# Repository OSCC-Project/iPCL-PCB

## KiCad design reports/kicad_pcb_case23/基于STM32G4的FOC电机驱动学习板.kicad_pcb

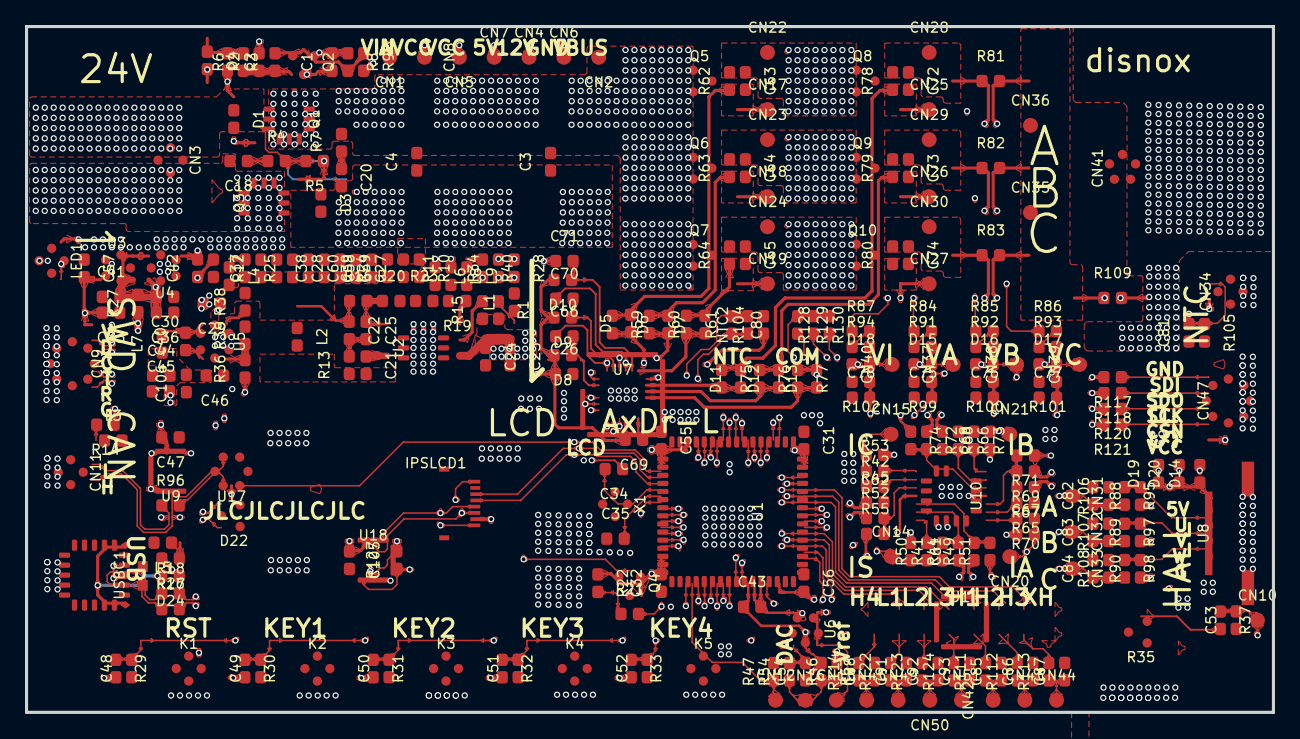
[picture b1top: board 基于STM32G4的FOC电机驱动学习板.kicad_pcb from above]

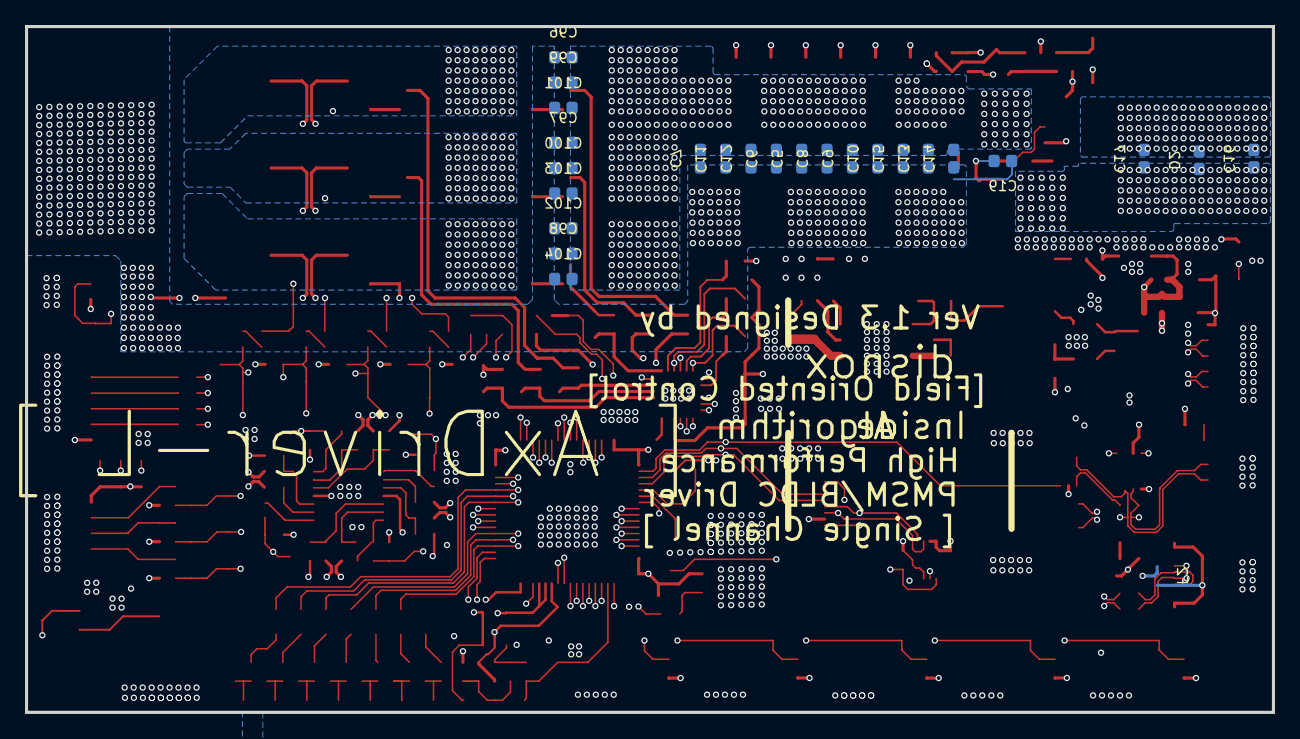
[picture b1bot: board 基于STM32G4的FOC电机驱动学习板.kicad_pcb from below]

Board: 4 copper layers, 100.0 x 55.0 mm, 334 parts (25 on the bottom side), 160 nets.

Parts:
C1, C2, C18, C19, C20, C26, C27, C28, C30, C31, C32, C33, C36, C37, C38, C39, C41, C42, C43, C44, C45, C46, C47, C48, C49, C50, C51, C52, C54, C55, C56, C57, C58, C59, C60, C61, C62, C63, C64, C65, C66, C67, C68, C69, C70, C71, C72, C73, C74, C75, C76, C77, C78, C80, C81, C82, C83, C84, C85, C86, C87, C88, C91, C92, C93, C105, C106: ef8bc71f18f14a2b8407a1c75c1857de
C3, C4: c59c3b7d6ca345ddb948f05971adbf39
C5, C6, C7, C8, C9, C10, C11, C12, C13, C14, C15, C16, C17, C29, C96, C97, C98, C99, C100, C101, C102, C103, C104: 562d9c395cfd4d56965eed8567f4960b
C21, C22, C25, C34, C35, C53: 7e8c87f61e8d48fe9289105f4e4eab7a
C23, C24: ac686b6caae446ffbbcca766a5ee3a01
C40: 47206a73ba6b4fccaee19337958ce421
CN1, CN2, CN4, CN5, CN6, CN7, CN8, CN10, CN12, CN13, CN14, CN15, CN16, CN17, CN18, CN19, CN20, CN21, CN22, CN23, CN24, CN25, CN26, CN27, CN28, CN29, CN30, CN31, CN32, CN33, CN35, CN36, CN37, CN38, CN39, CN40, CN42, CN43, CN44, CN45, CN49, CN50, CN51: fd3b323368aa491987dd5c73ade3f9d4
CN3: f1c4b56d3fa5492a905759f758d03d4e
CN9: e7604
CN11: e551
CN34: 72928b0395164ccbb3ac6d1df7a36019
CN41: 238db645694445ce824d8680ce8e221c
CN47: e0abee4a9a5b4604a238f3efeac42c31
D1, D3: 59eef894ab204f08bb19d40773817b76
D2: c2d7f1bae8b545698492e2dec6af670e
D4: 4f0528e9bede4f3ebeeda6dc7a85a460
D5, D6, D7, D11, D12, D13, D14, D15, D16, D17, D18, D19, D20, D24: f5361794368045b4a1b76496df9a3818
D8, D9, D10: 63cfcbcd9a284726b99ba225908b0e3a
D22: e166
F2: F0603
IPSLCD1: 焊接式_TFT_1.14_135X240_13PIN
J1: 507fd03bec4d44e5ae0a3a3c9a755e1a
K1, K2, K3, K4, K5: 38b16b919dc84e3a93c34e285811859a
L1, L3, L4, L5, L6, L8, L9: 15744c9fbac84e36ba33635dcccc2dd5
L2: 5eb3ba56938d4ba998db27fa04a57f61
L7: dccf333eac264c8c867efbfa5430a8ec
LED1: 92a6220bcf694ea1b484849a5b704caf
NTC2: 3ca690dd11e941f3ae1f3810a823019c
Q1, Q3: c54244fc48a749cda057cc0810780ba0
Q2: e50
Q4: e54
Q5, Q6, Q7, Q8, Q9, Q10: 5eed3b8ce67d409d8b6777258f1d9ffc
R1, R2, R3, R4, R5, R6, R7, R8, R9, R10, R11, R12, R14, R17, R18, R21, R22, R23, R24, R25, R26, R28, R29, R30, R31, R32, R33, R34, R37, R38, R40, R41, R42, R44, R45, R46, R47, R49, R50, R51, R52, R53, R54, R55, R57, R59, R60, R61, R62, R63, R64, R65, R66, R67, R68, R69, R70, R71, R72, R73, R74, R75, R76, R77, R78, R79, R80, R84, R85, R86, R87, R88, R89, R90, R91, R92, R93, R94, R95, R96, R97, R98, R99, R100, R101, R102, R104, R105, R106, R107, R108, R111, R112, R113, R114, R117, R118, R120, R121, R122, R123, R124, R127, R128, R129, R130: 3ca690dd11e941f3ae1f3810a823019c
R13, R15, R16, R19, R20: 7ca7a77a3c9a400a97f53773ae813252
R27, R36, R39: 7367616b648e4f089aa157a019dffa0b
R35: 079bee4ddd7a4396947f4deb10ada5d4
R81, R82, R83, R109: 9ad5a23cb50249ce82f923a95eb729c2
U1: e516
U2: 4fce1811ce044460a077a6a809735f86
U3: 2a1686e7c31848c09f9be7f9abc50536
U4: d97cf38101c64b749d9a7557fd111860
U5: 01fc61f14587464abc2342bbf474e4db
U6: d283220f0d3f47a3be0904fa3adf1f94
U7: 71895e02d11d4488b91a4eac142d4aa9
U8: conn-smd_5p-p1.25_xunpu_wafer-gh1.25-5pwb
U9: e3
U10: cc8f16f358a44a98967478fccaae8a8c
U17: 8034ca89fcaa42d08be80f2405998dfa
U18: 629a12d09f554d80887da3093acdb491
USBC1: e188
X1: 3fcb4c6e8928476cb18f6d5142511c4e

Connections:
5V: C30.2, C36.2, C41.2, C47.2, CN7.1, D14.1, D19.1, D20.1, D24.1, J1.15, LED1.3, R26.2, R27.2, U3.1, U3.3, U4.1, U4.3, U8.5, U9.3
12V: C22.1, C26.1, C27.2, C28.2, C29.2, C37.1, C38.2, C39.1, C58.2, C59.2, C60.2, C69.2, CN4.1, D8.2, D9.2, D10.2, L2.2, R16.1, R25.2, R38.2, U5.5, U7.4
$1N7256: C18.1, R4.1
$1N10553: C2.1, Q2.1, R2.1, R6.1
$1N11589: C19.1, D3.1, Q3.1, R5.1
$1N11866: D4.1, R3.1, R6.2
$1N12961: C20.1, R7.1
$1N15998: C2.2, Q2.3, R8.2, R9.1
$1N55849: C63.2, CN17.1, D5.2, Q5.1, R59.1, R62.1
$1N56388: C72.2, CN25.1, D11.2, Q8.1, R75.1, R78.1
$1N57486: C64.2, CN18.1, D6.2, Q6.1, R60.1, R63.1
$1N57488: C73.2, CN26.1, D12.2, Q9.1, R76.1, R79.1
$1N58344: C65.2, CN19.1, D7.2, Q7.1, R61.1, R64.1
$1N58346: C74.2, CN27.1, D13.2, Q10.1, R77.1, R80.1
$1N74659: R52.2, R55.2, U10.3
$1N75153: R42.2, R45.2, U10.2
$1N75339: R42.1, R53.2, U10.1
$1N78360: R41.1, R50.2, U10.7
$1N78363: R49.2, R51.2, U10.5
$1N78364: R41.2, R44.2, U10.6
$1N79721: R66.1, R73.2, U10.14
$1N79723: R72.2, R74.2, U10.12
$1N79724: R66.2, R68.2, U10.13
$1N80505: R65.1, R70.2, U10.8
$1N80507: R69.2, R71.2, U10.10
$1N80508: R65.2, R67.2, U10.9
$1N96819: R84.2, R91.1
$1N96824: R85.2, R92.1
$1N96829: R87.2, R94.1
$1N96834: R86.2, R93.1
$1N107842: R88.2, R95.1, U8.4
$1N108105: R89.2, R97.1, U8.3
$1N108370: R90.2, R98.1, U8.2
$1N130103: L9.1, R40.1
$1N130414: L8.1, R34.2
$1N134680: L5.1, R26.1
$1N145652: CN47.5, R117.1
$1N145656: CN47.4, R118.1
$1N145660: CN47.3, R120.1
$1N145664: CN47.2, R121.1
$1N245778: R36.2, R39.1, U5.3
$1N245779: C40.2, L7.1, U5.6
$1N245780: C40.1, U5.1
$1N268846: L3.1, R14.2
$1N269486: L1.1, R1.1
$1N270139: C85.1, CN42.1, R111.1
$1N270143: J1.9, R111.2
$1N270253: C91.1, CN49.1, R122.1
$1N270255: J1.3, R122.2
$1N270473: C86.1, CN43.1, R112.1
$1N270475: J1.11, R112.2
$1N270480: C92.1, CN50.1, R123.1
$1N270482: J1.5, R123.2
$1N270701: C87.1, CN44.1, R113.1
$1N270703: J1.13, R113.2
$1N270708: C93.1, CN51.1, R124.1
$1N270710: J1.7, R124.2
$1N398404: C1.2, D1.2, Q1.1, R8.1
$1N441583: C88.1, CN45.1, R114.1
$1N441584: J1.1, R114.2
$1N704042: L6.1, R28.1
$1N752227: CN16.1, R46.1, R54.1, R57.2
$1N807322: R35.2, R37.2
$1N846235: R38.1, U5.4
$1N858763: C54.2, R47.2, R54.2, U6.1
$1N920711: Q4.1, R21.1, R22.2
$1N958663: C44.2, C45.2, C46.2, C106.2, L7.2, R27.1, R36.1
$1N1062496: L4.1, R25.1
$1N1062500: R19.1, U2.4
$1N1062505: C22.2, C25.2, R13.2
$1N1062506: C21.2, L2.1, R13.1, U2.8
$1N1062507: R15.2, U2.3
$1N1062508: C21.1, U2.7
$1N1322078: R96.2, U17.4
$1N1473399: J1.16, R88.1, R89.1, R90.1
$1N1599202: D24.2, F2.2
ADSPE: C53.2, CN10.1, R37.1, U1.22
AGND: C42.1, C43.1, C54.1, C61.1, C62.1, C67.1, C68.1, R12.1, R57.1, U1.27, U6.2, U10.11
APH4: J1.2, U1.11
AVCC: C42.2, C43.2, CN8.1, R46.2, U1.28, U1.29, U4.5, U6.5, U10.4
BDM: R17.2, U1.45
BDP: R18.2, U1.46
CAN_H: CN11.2, D22.1, U9.7, U17.3
CAN_L: CN11.1, D22.2, R96.1, U9.6
CAN_RX: U1.61, U9.4
CAN_TX: U1.62, U9.1
CLK: CN9.3, U1.50
COM: R128.2, R129.1, R130.1, U1.26
DAC: CN12.1, R47.1, U1.18
DCBUS: C3.1, C4.1, C5.2, C6.2, C7.2, C8.2, C9.2, C10.2, C11.2, C12.2, C13.2, C14.2, C15.2, C23.2, C24.2, C96.2, C97.2, C98.2, C99.2, C100.2, C101.2, C102.2, C103.2, C104.2, CN2.1, Q1.2, Q5.2, Q6.2, Q7.2, R1.2, R2.2, R7.2, R15.1, R87.1, U2.2
DCBUS_IN: C1.1, C16.2, C17.2, CN1.1, CN3.1, D1.1, D2.2, Q1.3, Q2.2, R3.2, R4.2, R5.2
DIO: CN9.2, U1.49
FB: C25.1, R16.2, R20.1, U2.5
GND: C23.1, C24.1, C26.2, C27.1, C28.1, C29.1, C30.1, C31.1, C32.1, C33.1, C34.1, C35.1, C36.1, C37.2, C38.1, C39.2, C41.1, C44.1, C45.1, C46.1, C47.1, C48.1, C49.1, C50.1, C51.1, C52.1, C53.1, C55.1, C56.1, C57.1, C58.1, C59.1, C60.1, C69.1, C75.1, C76.1, C77.1, C78.1, C80.1, C81.1, C82.2, C83.2, C84.2, C85.2, C86.2, C87.2, C88.2, C91.2, C92.2, C93.2, C105.2, C106.1, CN6.1, CN9.6, CN9.7, CN9.8, CN11.3, CN11.4, CN34.3, CN34.4, CN47.6, CN47.7, CN47.8, D22.3, IPSLCD1.2, IPSLCD1.9, IPSLCD1.10, K1.1, K2.1, K3.1, K4.1, K5.1, L1.2, L3.2, L4.2, L5.2, L6.2, L8.2, L9.2, LED1.1, NTC2.2, R10.2, R11.2, R12.2, R19.2, R20.2, R23.1, R23.2, R24.1, R24.2, R35.3, R39.2, R99.2, R100.2, R101.2, R102.2, R105.2, R106.2, R107.2, R108.2, U1.15, U1.31, U1.47, U1.63, U2.1, U2.9, U3.2, U4.2, U5.2, U7.6, U7.25, U8.1, U8.6, U8.7, U9.2, U9.8, U9.9, U17.2, U18.4, U18.9, USBC1.0, USBC1.A1, USBC1.A12, USBC1.B1, USBC1.B12, X1.2, X1.4
HALL_A: C82.1, CN31.1, D19.2, R95.2, R106.1, U1.20
HALL_B: C83.1, CN32.1, D20.2, R97.2, R107.1, U1.21
HALL_C: C84.1, CN33.1, D14.2, R98.2, R108.1, U1.24
HIN1: J1.10, U1.42, U7.22
HIN2: J1.12, U1.43, U7.23
HIN3: J1.14, U1.44, U7.24
HO1: D5.1, R59.2, U7.19
HO2: D6.1, R60.2, U7.16
HO3: D7.1, R61.2, U7.13
IA: C67.2, CN20.1, R70.1, U1.14
IA+: C72.1, CN28.1, Q8.3, R69.1, R78.2, R81.1
IA-: CN35.1, CN36.1, R45.1, R49.1, R67.1, R68.1, R81.2, R82.2, R83.2, R109.1
IB: C68.2, CN21.1, R73.1, U1.13
IB+: C73.1, CN29.1, Q9.3, R72.1, R79.2, R82.1
IBUS: C61.2, CN14.1, R50.1, U1.17
IC: C62.2, CN15.1, R53.1, U1.12
IC+: C74.1, CN30.1, Q10.3, R52.1, R80.2, R83.1
KEY1: C49.2, K2.2, R30.1, U1.41
KEY2: C50.2, K3.2, R31.1, U1.40
KEY3: C51.2, K4.2, R32.1, U1.39
KEY4: C52.2, K5.2, R33.1, U1.38
LCD_BLK: R21.2, U1.60
LCD_CS: IPSLCD1.8, U1.59
LCD_DC: IPSLCD1.4, R40.2, U1.4
LCD_RES: IPSLCD1.3, R34.1, U1.3
LEDK: IPSLCD1.1, Q4.3
LIN1: J1.4, U1.35, U7.1
LIN2: J1.6, U1.36, U7.2
LIN3: J1.8, U1.37, U7.3
LO1: D11.1, R75.2, U7.11
LO2: D12.1, R76.2, U7.10
LO3: D13.1, R77.2, U7.9
MA: C63.1, C66.1, CN22.1, CN41.3, Q5.3, Q8.2, R62.2, R84.1, U7.18
MB: C64.1, C70.1, CN23.1, CN41.2, Q6.3, Q9.2, R63.2, R85.1, U7.15
MC: C65.1, C71.1, CN24.1, CN41.1, Q7.3, Q10.2, R64.2, R86.1, U7.12
NRST: C48.2, K1.2, R29.1, U1.7
NTC1: C80.2, NTC2.1, R104.2, U1.25
NTC3: C81.2, CN34.2, R105.1, U1.34
O_IN: C34.2, U1.5, X1.1
O_OUT: C35.2, U1.6, X1.3
PGND: C3.2, C4.2, C5.1, C6.1, C7.1, C8.1, C9.1, C10.1, C11.1, C12.1, C13.1, C14.1, C15.1, C19.2, C20.2, C96.1, C97.1, C98.1, C99.1, C100.1, C101.1, C102.1, C103.1, C104.1, CN41.4, CN41.5, D3.2, Q3.3, R9.2, R10.1, R11.1, R44.1, R109.2
PGND_IN: C16.1, C17.1, C18.2, CN3.2, D2.1, D4.2, Q3.2
RGB: LED1.2, U1.19
RX_TX: CN9.5, U1.33
R_EN: R28.2, U1.2, U17.6
SPI1_CSN: R121.2, U1.55
SPI1_MISO: R118.2, U1.57
SPI1_MOSI: R117.2, U1.58
SPI1_SCK: R120.2, U1.56
SPI3_CSN: R127.1, U1.51, U18.1
SPI3_MISO: U1.53, U18.2
SPI3_MOSI: IPSLCD1.5, U1.54, U18.5
SPI3_SCK: IPSLCD1.6, U1.52, U18.6
TX_RX: CN9.4, U1.30
USB_5V: F2.1, USBC1.A4, USBC1.A9, USBC1.B4, USBC1.B9
USB_DM: R17.1, USBC1.A7, USBC1.B7
USB_DP: R18.1, USBC1.A6, USBC1.B6
VA: C75.2, CN37.1, D15.2, R91.2, R99.1, R128.1, U1.8
VB: C76.2, CN38.1, D16.2, R92.2, R100.1, R130.2, U1.9
VB1: C66.2, D8.1, U7.20
VB2: C70.2, D9.1, U7.17
VB3: C71.2, D10.1, U7.14
VBUS: C78.2, CN40.1, D18.2, R94.2, R102.1, U1.23
VC: C77.2, CN39.1, D17.2, R93.2, R101.1, R129.2, U1.10
VCC: C31.2, C32.2, C33.2, C55.2, C56.2, C57.2, C105.1, CN5.1, CN9.1, CN34.1, CN47.1, D15.1, D16.1, D17.1, D18.1, IPSLCD1.7, Q4.2, R14.1, R22.1, R29.2, R30.2, R31.2, R32.2, R33.2, R35.1, R104.1, R127.2, U1.1, U1.16, U1.32, U1.48, U1.64, U3.5, U9.5, U17.5, U18.3, U18.7, U18.8
VREF: CN13.1, R51.1, R55.1, R71.1, R74.1, U6.3, U6.4

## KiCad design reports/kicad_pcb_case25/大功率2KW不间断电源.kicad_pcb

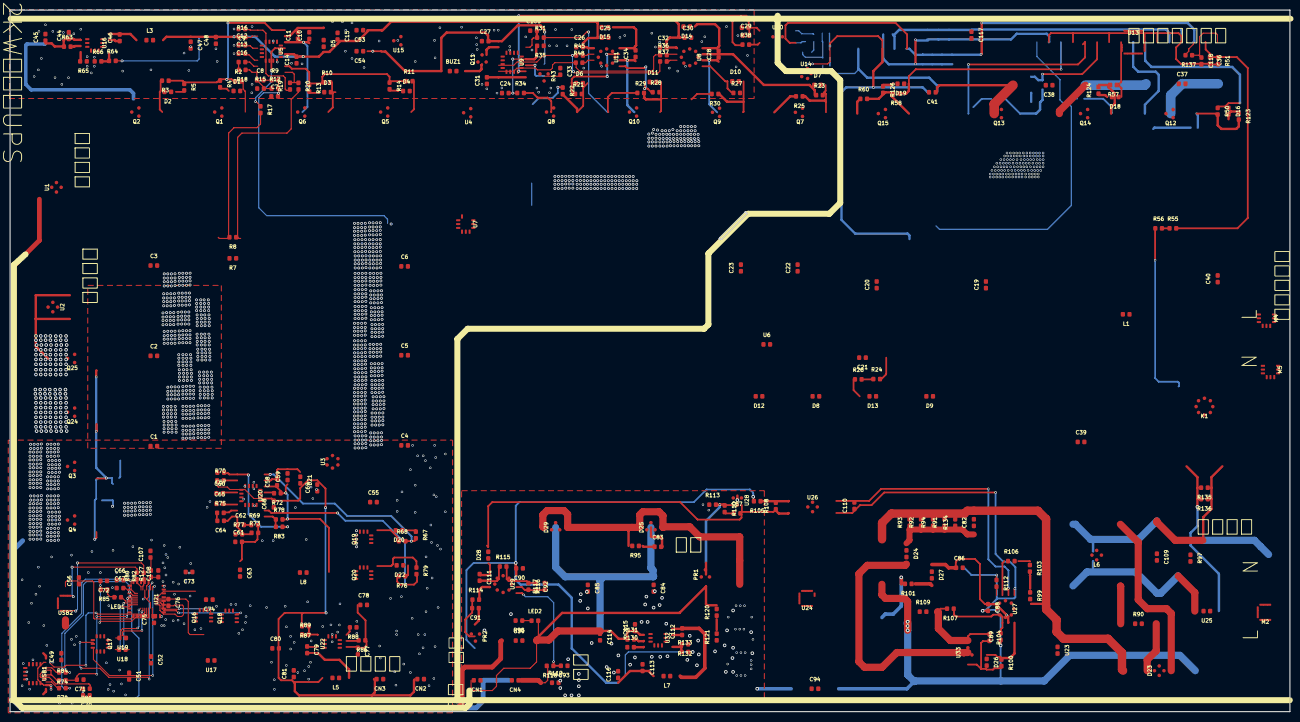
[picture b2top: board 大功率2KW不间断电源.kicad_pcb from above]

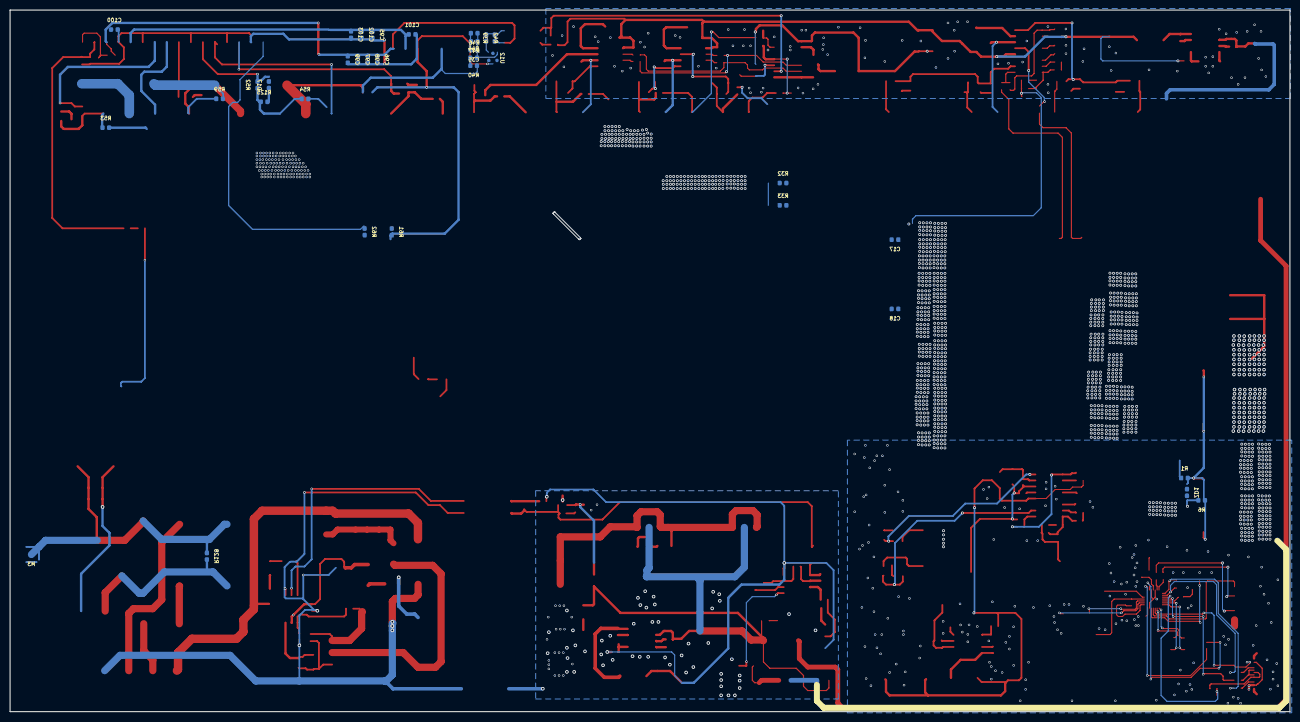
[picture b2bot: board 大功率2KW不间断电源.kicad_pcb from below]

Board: 4 copper layers, 270.0 x 148.0 mm, 350 parts (34 on the bottom side), 196 nets.

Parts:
BUZ1: 981fdc45c260454382e9b75324f64161
C1, C2, C3, C4, C5, C6: c78e01ed92c84e84b7a0ad6141ebd8fd
C7: e13
C8, C9, C12, C16, C61: 625d24b7aa0746d79cb1a7612a5a842d
C10: e18
C11: e47
C13, C14, C24, C26, C27, C29, C31, C32, C33, C35, C36, C44, C46, C48, C52, C58, C66, C67, C70, C71, C72, C74, C75, C76, C77, C79, C80, C87, C88, C89, C90, C91, C92, C93, C106, C107, C108, C110, C111, C112, C113, C115, C118: 0545a2ef202b483fbcb0fbb80e857793
C15: e50
C17, C18: b3456f740354439e9160aa180bb48eb0
C19: e58
C20: e67
C21: 09857c8ff61a4d6a9579135719eb9d0b
C22, C23: 1a0531ca59184fc29a1c54a4e021815c
C25: e111
C28: e108
C30: e110
C34: e109
C37, C38, C40, C109: ceb86e31d49f43e3a9040d39437dd5e7
C39: eb88e0adea434af087092e3f79bb7bfc
C41, C86, C117: 2f6db40664434af5b126b81886d49525
C45, C78, C114: 1b2a19af337d4bedb8a0b6d22609e00e
C47: e57
C49, C65, C83, C95, C96, C97, C98, C99, C100, C101, C102, C103: 6d7162d10f8a45cd8359ab79cce4e34e
C51: e41
C53, C54: b1cbfb15478b4242a6341a524d2da4a9
C55: e203
C56: e243
C57: e201
C59: e200
C60: e187
C62: e207
C63, C73: c73c13185889447a876a17b5cc692504
C64: e190
C68: e204
C69: e205
C81: e219
C82: fdd47064da444262bb87db789fc3cbfa
C84, C85: 484aa3d6da3141ca93b2f63d33b33dab
C94: d28f21b4a1ab4d38a267425a96ac73d7
C116: b0047ecd2bd1495bbe1332fb317f2c6e
CN1, CN2, CN3, CN4: 4409cd7d75a24d899561e1afd9d0c91d
D1: e31
D2: e34
D3: e10
D4: e37
D5: b7e40c2316e041f9ae8b72650a3f28df
D6: e65
D7: e61
D8, D9, D12, D13: 3aead71d3d0a408fa66ded00cf7ef2c0
D10: e59
D11: e63
D14: e106
D15: 723ca1bf1608410eb545f3d7b29f9995
D16: e152
D17, D18, D19: 0de8eb6981de47368f80bf173eed7f6d
D20: e186
D21: e199
D22: e210
D23: e701497ac61442a6a7d2d42a0fe4ddf8
D24, D27: 3c6509dabff244568e2ad9413914b7a9
D25, D29: a9163deda7a84cfdb29bed682bde033e
D26: c96edb59553643ac86e1d72e2344cdfe
D28: e357
K1: e861ec74aeaa4749a7bad2f82d4f7d1b
L1: 21bc3348aefd461e8ec269683d106a9b
L3, L5, L7: 4e5b1be01e154a1aae79930a1ca4dbbf
L6: 23be79adb1ff402bbee92d870da0044f
L8: 6eb655b0784a4c989c80c2383f69ee80
LED1, LED2: e056186051ed4454bf2d51e82629d28c
M2, M3, M4, M5: 15c72e44ad514418ba3ebf88d3d8100d
PR1: 4d896ef86762449aa96044e52afce319
PR2: e362
Q1, Q2, Q5, Q6, Q7, Q8, Q9, Q10: 6ee70a0dc2f0407d922e7886ff4b23f3
Q3, Q4, Q24, Q25: 229498eea7964205ac0b97ba6f749a00
Q11: 75d96634697b4ea48933bc3cf3406ffc
Q12, Q13, Q14, Q15: be96e469609c40b38bb54d3074a85c5f
Q16, Q18: 64cfd75dc56148639c580ca769c26c6e
Q17: 773db1cdd5284d6ba304d87793fff29c
Q19: 5af63b759e584252a405bd05bc2521ab
Q20: e197
R1, R6, R15, R17, R19, R20, R31, R34, R35, R36, R37, R38, R39, R40, R41, R42, R44, R45, R46, R47, R48, R51, R53, R54, R55, R56, R59, R60, R63, R64, R65, R66, R71, R74, R77, R80, R81, R82, R83, R84, R85, R86, R87, R88, R89, R98, R104, R105, R107, R108, R110, R112, R113, R114, R115, R116, R117, R118, R127, R130, R131, R132, R133: 2b75900dce304d8d9542e1853d69f89c
R2: e32
R3: e35
R4: e33
R5: e36
R7, R8, R32, R33, R61, R62: d9dde99a41734b1480e16ee5d1b02dd3
R9, R16, R18, R69, R78: f69ec4d18ed54d53be30b53e3652fffb
R10: e29
R11: e38
R12: e14
R13: e30
R14: e39
R21: e66
R22: e71
R23: e62
R24: e97
R25: e68
R26: e98
R27: e60
R28: e64
R29: e70
R30: e69
R43: 9461965dc73a4c33b493aeb56ceb5153
R50: e150
R52, R57, R123, R124, R125, R128: 03263ca126db421d9bfe7ce0ea3da3c5
R58: e154
R67: e208
R68: e209
R70: e195
R72: e202
R73: e192
R75: e189
R76: e211
R79: e212
R90: 3741a20861444a298abb5fb1f972a81c
R91, R92, R93, R94, R95, R99, R101, R103, R106, R120, R121, R134, R135, R136: f13a3459929c404584fa8917de07ebdf
R97: 614ba737c8e6452abf81a855fe5fe8ed
R100: e545
R109: 6120b3945c8a4423a863e0972eaa40cb
R119: ab741e0fbb424d2aa33a5e4a59c24107
R126: e347
R137: 9cdc9b2ee6714f45a09f03c4f5147ae0
U1, U2: eed239c8ae604fccb6fee79c821defa3
U3: 08084aac675441a3b2a13dc01140b903
U4: 996f1ad84f4545cd9b531c6575053a52
U5: 93aa71a2e1ae49c6b705c184138b5e10
U6, U17: 1652358d6c30419882f4d2f1029b7bab
U7: e80
U8, U11: ba12130b8e92436f93284fa39be100a3
U9: e96
U10: 419a7336aa0342d99064abcfa8fc7525
U12: 45445f4c9ce44868a7effe3a6008a06c
U13: 4bf99dcbd7694ef0a1965c6941c92f9a
U14: ff6b5b503b584451bf00b751f0efbcc5
U15: 60ddd3f7649a424b8478f7033c3471e3
U16, U22, U32: f3ec1248765745f7b91ce87cd3477772
U18, U19: f13a3459929c404584fa8917de07ebdf
U20: e194
U21: cdc4d2913dbd49489142be1bb003ce76
U23: 6886ed53101c48d782a0891e76799d56
U24: 6f8c06f4de764626a986deb7067376b9
U25: 0dcd430ebd604fbca7c448f9df85bd97
U26: 186e16484ecb48d7b155389c9e2d2946
U27: 6768cf3358e94dc8b6aaa92e1a1c4ba2
U28: 75d96634697b4ea48933bc3cf3406ffc
U29: 578aa49ba62144c9a7eb08856a25eaef
U30: a8c63376e0b24dfc8a17c2b20e46163c
U33: 8af857738e2c44c3a8f520dc9f4b3662
USB1: 0d34a4ee21af46c38cceb6a036d97f3c
USB2: fb82d49e9a7c4f358102e5c401603f27
ZD1: 07125ebaec034e33bcabed52f075c14f

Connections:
48-72V: C1.1, C2.1, C3.1, C44.1, C45.1, Q1.2, Q2.2, R1.2, R63.1, U1.1, U1.2, U1.3, U1.4, U16.2, U30.1
$1N1866: R19.2, R20.1, U5.9
$1N1868: R16.2, U5.2
$1N1874: C13.2, U5.6
$1N1875: C12.2, U5.4
$1N1897: C8.2, R9.1
$1N2706: D3.1, R13.2
$1N2714: D3.2, Q6.1, R10.2
$1N2902: D1.1, R4.2
$1N2907: D1.2, Q1.1, R2.2
$1N3282: D2.1, R5.2
$1N3287: D2.2, Q2.1, R3.2
$1N3377: D4.1, R14.2
$1N3382: D4.2, Q5.1, R11.2
$1N4013: R17.1, U5.13
$1N4084: C10.2, C11.2, D5.1, U5.15
$1N8973: C16.1, R18.2
$1N9019: C16.2, U5.7
$1N24864: Q3.1, Q4.1, Q24.1, Q25.1, R1.1, R6.2, ZD1.2
$2N1982: Q9.3, Q10.3, R29.1, R30.2, R31.2, R32.2, R33.2
$2N1991: D9.2, D13.1, U7.4
$2N3168: U6.1, U7.3
$2N3195: C22.2, C23.2, D8.2, D12.1
$2N3310: C22.1, C23.1, U6.2
$2N4836: R24.1, R26.2
$2N6916: R36.2, U8.2
$2N6919: R37.2, U8.3
$2N7016: R36.1, R48.1, U9.6
$2N7024: R37.1, R45.1, U9.5
$2N7037: R45.2, U11.2
$2N7040: R48.2, U11.3
$2N7298: C28.2, D14.1, U8.8
$2N7355: C34.2, D15.1, U11.8
$2N7667: C31.2, U9.7, U9.10
$2N8060: C24.2, R34.1, R35.2, U9.13
$2N8362: R39.1, R42.2, U10.2
$2N8432: R42.1, U12.2
$2N8648: R40.1, R44.2
$2N8733: C35.2, R44.1, R46.2, R47.2, U12.1
$2N8791: R38.2, U10.4
$2N9341: BUZ1.2, Q11.3
$2N9391: Q11.1, U9.2
$2N27579: D11.2, Q10.1, R28.2, R29.2
$2N27600: D6.2, Q8.1, R21.2, R22.2
$2N27609: D7.2, Q7.1, R23.2, R25.1
$2N27625: D10.2, Q9.1, R27.2, R30.1
$3N5649: Q13.1, R52.2, R54.2, R125.2
$3N5677: D16.1, R50.1, U13.10
$3N5683: L1.2, Q12.3, Q14.2, R53.1, U13.9
$3N5698: D18.1, R57.1, U13.8
$3N5704: D17.1, R52.1, U13.6
$3N5727: D19.1, R58.1, U13.3
$3N5901: R55.1, R56.2
$3N5967: C36.1, R51.1, R55.2, U13.15
$3N7425: C37.1, C38.1, Q14.3, Q15.3, R59.1, R60.1, R61.2, R62.2, U13.1
$3N11214: D17.2, R125.1
$3N11217: Q15.1, R58.2, R60.2, R126.2
$3N11223: D19.2, R126.1
$3N11226: Q14.1, R57.2, R59.2, R124.2
$3N11232: D18.2, R124.1
$3N11235: Q12.1, R50.2, R53.2, R123.2
$3N11240: D16.2, R123.1
$3N13399: C112.1, U32.7
$3N13400: C112.2, L7.1, U32.8
$3N13401: R130.2, U32.4
$3N13404: R131.2, U32.3
$3N13407: R132.2, R133.1, U32.5
$3N15793: C118.1, R137.1, U13.16
$4N1079: C46.1, U16.7
$4N1082: C46.2, L3.1, U16.8
$4N1143: R65.2, U16.4
$4N2447: R70.2, U20.2
$4N2448: R75.2, U20.7
$4N2451: C64.2, R75.1
$4N2453: C65.2, U20.6
$4N2454: C60.2, U20.4
$4N2463: R72.2, U20.13
$4N2476: C62.2, R69.1
$4N2542: D20.1, R67.1
$4N2570: D20.2, Q19.4, R68.1
$4N2663: D22.1, R76.1
$4N2665: D22.2, Q20.4, R79.1
$4N3192: R76.2, R79.2, U20.10
$4N3246: R67.2, R68.2, U20.16
$4N3287: C58.1, C59.1, L8.1, Q19.1, Q19.2, Q19.3, Q20.5, Q20.6, Q20.7, Q20.8, Q20.9, R72.1, R78.2, U20.14
$4N3376: R78.1, R83.2, U20.9
$4N3820: R63.2, U16.3
$4N3977: R64.1, R66.2, U16.5
$4N4171: C58.2, C59.2, D21.1, U20.15
$4N4920: C75.2, U21.14
$4N7910: R80.1, U21.28
$4N7969: R82.1, U21.27
$4N8032: C76.2, U21.15
$4N9834: C70.2, R81.2, U21.3
$4N9841: C71.2, R84.2, U21.4
$4N14125: LED1.2, R85.1
$4N14153: C72.2, R85.2, U21.12
$4N21735: C79.1, U22.7
$4N21736: C79.2, L5.1, U22.8
$4N21737: R88.2, U22.4
$4N21740: R86.2, U22.3
$4N21743: R87.1, R89.2, U22.5
$4N43359: C107.1, R127.2
$4N43398: C108.1, R127.1, U21.25
$5N8672: K1.5, M5.1
$5N8675: K1.6, M4.1
$5N11155: LED2.1, R98.1
$5N14086: D26.2, R100.2, R104.2, U33.1
$5N14089: R112.2, U27.4
$5N14102: D24.2, U24.3, U33.2
$5N14105: D23.1, R90.2
$5N14110: D27.2, R101.1
$5N14111: R101.2, U24.1
$5N14113: R106.1, U27.3
$5N14114: R103.1, R106.2
$5N14115: R99.1, R103.2
$5N14116: C82.2, D23.2, R91.2, R92.2, R93.2, R94.2, R99.2, R134.2, U23.1, U24.4
$5N14121: C89.2, R107.1, U27.6
$5N14128: C83.1, R95.1
$5N17421: D25.1, D25.3, D29.1, D29.3, R95.2, U24.5, U24.6, U24.7
$5N17837: R104.1, R107.2, R109.2, U33.3
$5N21264: C87.1, R110.2
$5N21265: R105.1, R108.2, U26.1
$5N21268: C87.2, D28.2, R108.1, U26.2, U28.2
$5N21271: R114.2, U29.3
$5N21273: C91.2, PR2.2, R114.1
$5N21278: C92.1, R115.2, R116.1, U29.7
$5N21281: C92.2, R116.2, R117.1, U29.6
$5N21306: C110.2, U26.4, U27.2
$5N21369: PR1.2, PR1.3, R110.1, R113.2, U28.1
$5N21674: R120.1, R121.2
$5N21739: CN4.2, R118.2, R119.1
$5N27987: C111.1, D28.1, U29.1
$5N27996: C111.2, R115.1, U29.2
$5N28177: C93.2, R118.1, U29.5
$5N28266: D23.3, L6.1
$5N28275: L6.4, R90.1
$5N28284: C109.2, L6.3, R97.2, R128.1, U25.2
$5N29963: C82.1, D24.1, R91.1, R92.1, R93.1, R94.1, R134.1
$5N36391: D26.1, R100.1, U27.8
+5V: BUZ1.1, C27.2, C54.1, R43.1, U9.1, U15.3
+5V2: C57.1, R83.1, U20.1
+12V: C14.2, C15.2, C25.1, C26.2, C30.1, C32.2, C47.1, C48.2, C53.1, D5.2, D14.2, D15.2, L3.2, R16.1, R38.1, R64.2, U5.12, U8.1, U11.1, U15.1
+12V2: C68.2, C69.2, C80.2, C81.1, CN2.1, CN3.1, D21.2, L5.2, R70.1, R87.2, U20.12
+12V3: C90.2, C113.2, C116.1, L7.2, PR2.3, R105.2, R133.2, U29.8
+24.5V: C61.2, C63.1, C73.1, C74.2, L8.2, Q16.5, Q16.6, Q16.7, Q16.8, R69.2, R73.2, U21.19
+48V: C4.1, C5.1, C6.1, C7.2, C17.2, C18.2, C55.1, C77.1, C78.1, Q7.2, Q8.2, Q19.5, Q19.6, Q19.7, Q19.8, Q19.9, R9.2, R12.2, R34.2, R86.1, U3.2, U22.2
+400V: C19.1, C20.1, C21.1, C37.2, C38.2, C41.1, D8.1, D9.1, Q12.2, Q13.2, R24.2, R40.2, U14.1
+H5V: C96.2, C97.2, C98.2, C99.2, C100.2, R39.2, R137.2, U10.1, U13.14, U14.5
+H15V: C95.2, C101.2, C102.2, C103.2, C117.1, U13.12, U14.4
AC_L: C39.2, C40.2, K1.4, L1.1, R56.1
AC_N: C39.1, C40.1, K1.3, Q13.3, Q15.2, R54.1, U13.5
BAT_G: CN1.2, CN4.1, Q3.2, Q4.2, Q24.2, Q25.2, U2.1, U2.2, U2.3, U2.4
BGND: C84.2, C85.2, C90.1, C91.1, C93.1, C94.1, C113.1, C114.2, C115.2, C116.2, PR2.1, R98.2, R113.1, R117.2, R119.2, R121.1, R130.1, R132.1, U24.8, U24.9, U24.10, U28.3, U29.4, U32.1, U32.9
CC1: C67.2, R74.1, U21.2
CC1R: R74.2, USB1.A5
CC2: C66.2, R71.1, U21.1
CC2R: R71.2, USB1.B5
CGND: C86.2, C88.2, C89.1, C94.2, C110.1, D23.4, R109.1, R112.1, U23.2, U24.2, U26.3, U27.1
CSNA: Q17.7, Q17.8, U19.2, U21.8
CSNC: Q17.5, Q17.6, U18.2, U21.7
CSPC: C51.1, C52.2, U17.2, U18.1, U19.1, U21.6, U21.9
DMAR: R80.2, USB2.2
DMCR: R84.1, USB1.A7, USB1.B7
DPAR: R82.2, USB2.4
DPCR: R81.1, USB1.A6, USB1.B6
FADJ: C33.2, R43.2, U9.12
FLYBUCK: C83.2, C84.1, C85.1, C114.1, C115.1, CN1.1, D25.2, D29.2, LED2.2, PR1.1, R120.2, R131.1, U30.2, U32.2
GATEA: Q17.2, U21.23
GATEC: Q17.4, U21.22
GND: C1.2, C2.2, C3.2, C4.2, C5.2, C6.2, C7.1, C9.2, C12.1, C13.1, C14.1, C15.1, C17.1, C18.1, C24.1, C25.2, C26.1, C27.1, C29.1, C30.2, C31.1, C32.1, C33.1, C44.2, C45.2, C47.2, C48.1, C49.2, C51.2, C52.1, C53.2, C54.2, C55.2, C56.2, C57.2, C60.1, C61.1, C63.2, C65.1, C66.1, C67.1, C68.1, C69.1, C70.1, C71.1, C72.1, C73.2, C74.1, C75.1, C77.2, C78.2, C80.1, C81.2, C106.1, C107.2, C108.2, CN2.2, CN3.2, Q3.3, Q4.3, Q5.3, Q6.3, Q11.2, Q18.1, Q18.2, Q18.3, Q20.1, Q20.2, Q20.3, Q24.3, Q25.3, R6.1, R15.1, R32.1, R33.1, R35.1, R41.1, R43.3, R65.1, R66.1, R77.1, R88.1, R89.1, U4.1, U4.3, U5.3, U5.5, U5.11, U8.4, U9.14, U9.16, U11.4, U15.4, U16.1, U16.9, U20.3, U20.5, U20.11, U21.13, U21.24, U21.26, U21.29, U22.1, U22.9, USB1.1, USB1.2, USB1.3, USB1.4, USB1.A1B12, USB1.B1A12, USB2.5, USB2.6, USB2.7, USB2.8, USB2.9, ZD1.1
HGATE: Q16.4, U21.17
HO1: D6.1, R21.1, U11.7
HO2: D7.1, R23.1, U8.7
IDC: LED1.1, U21.5
IN_L: K1.2, K1.8, M2.1, R135.2, R136.2, U25.1
IN_N: C109.1, K1.1, K1.7, L6.2, M3.1, R97.1, R128.2, R135.1, R136.1
LFB: C62.1, C64.1, R73.1, R77.2, U20.8
LGATE: Q18.4, U21.16
LHO1: R2.1, R3.1, R4.1, R5.1, U5.16
LLCIFB: C106.2, R31.1, U9.15
LLFB: C8.1, R12.1, R15.2, R18.1, U5.8
LLO1: R10.1, R11.1, R13.1, R14.1, U5.10
LO1: D11.1, R28.1, U11.5
LO2: D10.1, R27.1, U8.5
PGND: C19.2, C20.2, C21.2, C35.1, C36.2, C41.2, C95.1, C96.1, C97.1, C98.1, C99.1, C100.1, C101.1, C102.1, C103.1, C117.2, C118.2, D12.2, D13.2, R26.1, R46.1, R47.1, R51.2, R61.1, R62.1, U12.3, U13.2, U13.4, U13.7, U13.11, U13.13, U14.3
REF5: C9.1, R19.1, U5.1
SDHIN: Q1.3, Q2.3, R7.2, R8.2, R17.2
SDLIN: C10.1, C11.1, Q5.2, Q6.2, R7.1, R8.1, R20.2, U3.1, U4.2, U5.14
SW: C76.1, Q16.1, Q16.2, Q16.3, Q18.5, Q18.6, Q18.7, Q18.8, U17.1, U21.18
VBUSA: C56.1, Q17.1, U21.11, USB2.1
VBUSC: C49.1, Q17.3, U21.10, USB1.A4B9, USB1.B4A9
VDD: C86.1, C88.1, D27.1, U27.7
VFB: C29.2, R41.2, U9.11, U10.3
VS1: C34.1, Q8.3, Q10.2, R22.1, U7.2, U11.6
VS2: C28.1, Q7.3, Q9.2, R25.2, U7.1, U8.6

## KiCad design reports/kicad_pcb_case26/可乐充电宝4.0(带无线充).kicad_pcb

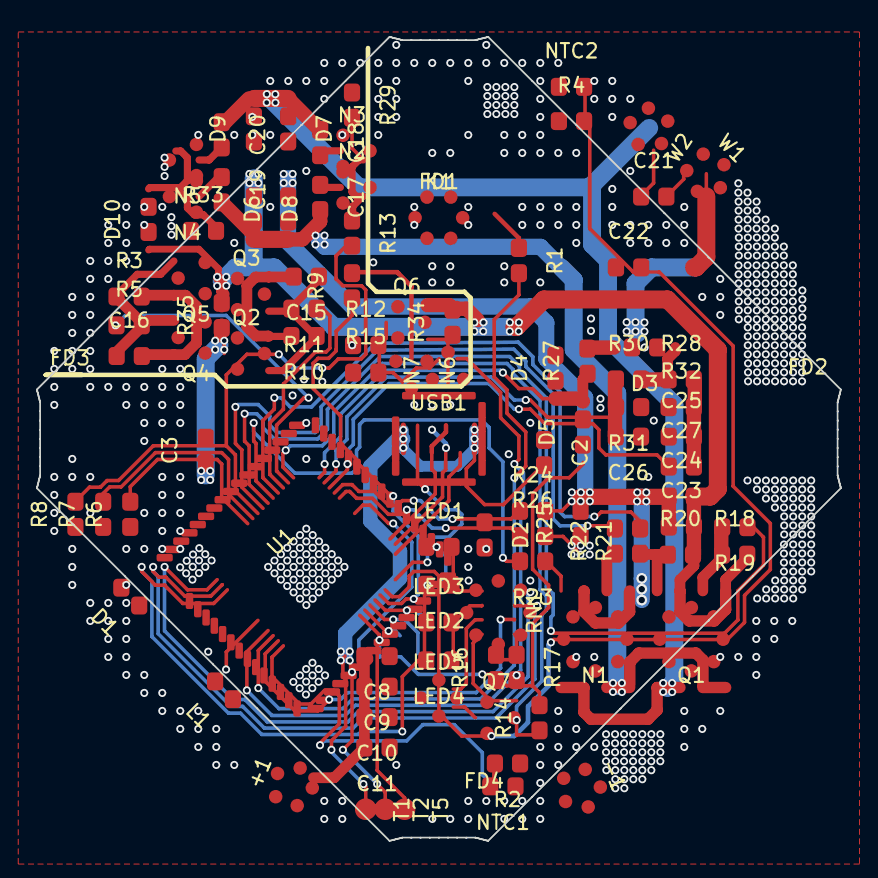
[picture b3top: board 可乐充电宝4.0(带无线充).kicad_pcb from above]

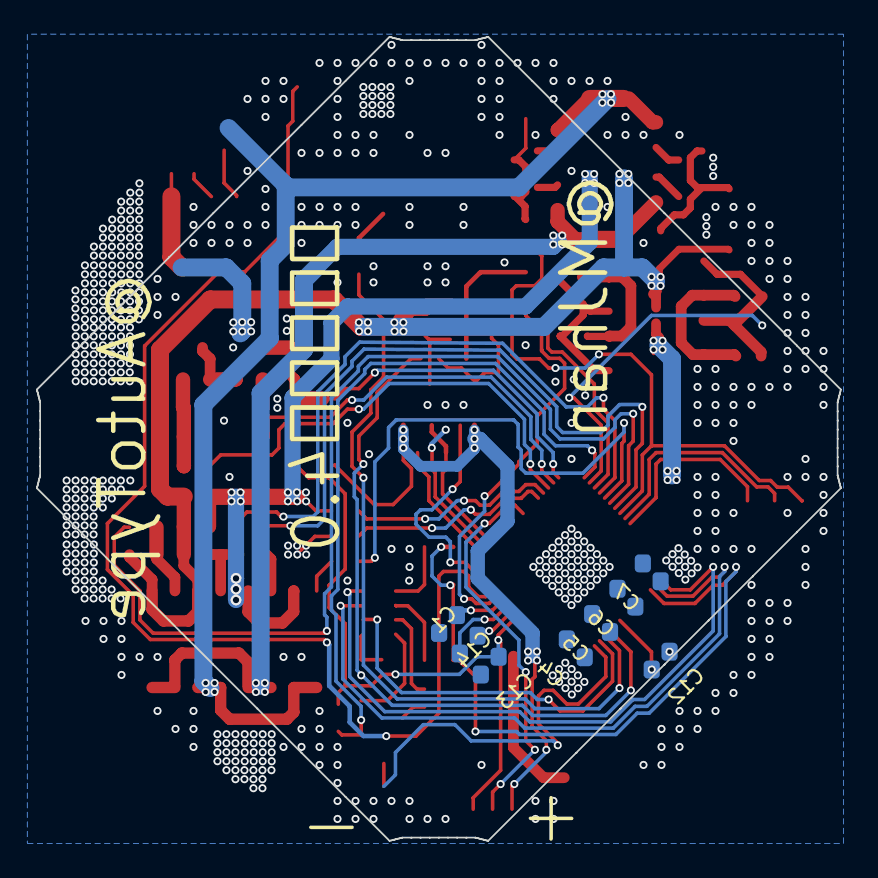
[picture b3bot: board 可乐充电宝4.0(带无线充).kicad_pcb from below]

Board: 4 copper layers, 44.7 x 44.7 mm, 109 parts (8 on the bottom side), 70 nets.

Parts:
+1: e92
-1: e5ea5c940935493f8f3948bb46106a8b
C1, C2, C12, C13, C14, C15, C16, C17, C18, C19, C20, C21: 13657908e64b43e38100a7258f2a1308
C3: e56
C4, C5, C6, C7: 709eea73d59b4e69827828ea959a58ab
C8: e66
C9: e68
C10: e70
C11: e72
C22: c51ab6312978470f846005bc3928b202
C23: e316
C24: e318
C25: e338
C26: e340
C27: e344
D1: fb01f6408f9644b68647b4d7d7bbe397
D2: f2fc549e2e644821a5ebeae223070784
D3: e57
D4, D5, D10: 1503a6aeeaef490788caadf9e1584eea
D6: e273
D7, D8, D9: dc7975ced9e240f48fafaa481643820d
FD1: e89
FD2: e90
FD3: e91
FD4: e88
K1: e1
L1: 8127617852484fe28a00c89d9f54357e
LED1: e76
LED2: e80
LED3: e78
LED4: 3505c783f57740079868554e02f91a31
LED5: e84
N1: e241
N2, N3, N4, N5, N6: 2157e94d48ac4c20bb50a778953db69b
N7: e253
NTC1, NTC2: 3f4bf36c4f38493a97bcc9be5c111ba0
Q1: e243
Q2, Q3, Q4, Q5: 721ce78deaeb48a688b6db6df8ffdbe9
Q6: e237
Q7: 3223676d680544e09480d895e02a5bb1
R1, R2, R3, R4, R5, R6, R7, R8, R10, R11, R13, R14, R22, R23, R24, R26, R29, R30, R31, R33: 6896e77e52a047b5a4fc8453da59758e
R9: e42
R12: e255
R15: e289
R16: e4
R17: 4ec273b111064d29abd98e5be984a8c6
R18: e308
R19: e310
R20: e312
R21: e314
R25: 1af17e4be3844eb9b4027a00138b9177
R27: e330
R28: e332
R32: e342
R34: e285
R35: e353
RN1: c110a20addcf4e749a2bb65bc0b38850
T1, T2, T5: 8d1c1508188040a881611b22b7531904
U1: e104
USB1: e211
W1, W2: e5ea5c940935493f8f3948bb46106a8b

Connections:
$2N226: C1.1, U1.26
$2N227: C1.2, U1.27
$2N393: LED3.2, LED4.1, RN1.2
$2N406: LED1.2, LED2.1, RN1.1
$2N19913: C15.2, Q2.2, Q3.2, R10.2
$2N20622: C15.1, Q2.1, Q3.1, R10.1, R11.2
$2N22161: C16.1, Q4.1, Q5.1, R3.1, R5.2
$2N22162: C16.2, Q4.2, Q5.2, R3.2
$2N45797: N2.1, N3.1, R13.1, R29.2
$2N48937: D10.2, N4.1, N5.1, R33.2
$2N50148: C17.1, N2.3
$2N50254: C18.2, N3.3
$2N51175: C20.2, N5.3
$2N51282: C19.1, N4.3
$2N64070: N7.3, Q6.1, R34.1
$2N64496: N6.1, N7.2, Q6.3, R12.2, R15.2
$2N74749: LED5.1, Q7.3
$2N88992: Q1.2, R18.1, R19.2
$2N91119: Q1.4, R20.1, R21.1
$2N108755: N1.4, R23.1
$2N108929: N1.2, R22.1
$2N112597: D3.1, R28.1, R30.2
$2N116781: C25.2, C27.2, R28.2, R32.2
AUXDRV1: R11.1, U1.51
AUXDRV2: R5.1, U1.50
AUXDRV3: Q7.1, R14.1, U1.49
B: Q7.2, RN1.4
BAT: +1.1, +1.e5, +1.e7, +1.e8, +1.e9, C8.2, C9.2, C10.2, C11.2, L1.1, U1.23, U1.24
BST: C12.1, U1.9
CC1: U1.32, USB1.A5
CC2: U1.33, USB1.B5
COIL_I: C23.1, C24.1, D6.2, D7.2, N1.1, N1.3, R24.2, R25.2
COIL_V: C21.2, C22.2, D3.2, R27.2, W1.1, W1.e5, W1.e7, W1.e8, W1.e9
CTR_B: R16.2, R17.1, RN1.5
DMC: U1.35, USB1.A7, USB1.B7
DNGATE1: R22.2, U1.55
DNGATE2: R23.2, U1.53
DPA2: T2.1, U1.41
DPC: U1.34, USB1.A6, USB1.B6
FCAP: R8.2, R13.2, U1.56
FOD_DET: D4.1, D5.2, R27.1, U1.48
G: LED5.2, RN1.3
GND: -1.1, -1.e5, -1.e7, -1.e8, -1.e9, C2.1, C3.2, C4.1, C5.1, C6.1, C7.1, C8.1, C9.1, C10.1, C11.1, C13.1, C14.1, C25.1, C26.1, D1.2, D2.1, D4.2, K1.3, K1.5, LED5.3, LED5.4, N2.2, N3.2, N4.2, N5.2, N6.2, NTC1.1, NTC2.1, R2.1, R4.1, R6.1, R7.1, R8.1, R12.1, R15.1, R25.1, R26.2, R29.1, R31.1, R32.1, R33.1, U1.10, U1.43, U1.65, USB1.0, USB1.A1, USB1.A12, USB1.B1, USB1.B12
HLED: R1.2, U1.12
IGND: R26.1, U1.44
ISENSE: R24.1, U1.45
KEY: R9.1, U1.29
KEY_1: K1.2, N6.3, R9.2
KEY_MODE: R6.2, U1.58
LED1: RN1.8, U1.1
LED2: RN1.7, U1.2
LED3: LED1.1, LED2.2, LED3.1, LED4.2, U1.3
LED_G: RN1.6, U1.13
LED_H: K1.6, R1.1
LED_R: N7.1, R17.2, U1.11
LX: C12.2, D1.1, L1.2, U1.4, U1.5, U1.6, U1.7, U1.8
NTC1: NTC1.2, R2.2, U1.14
NTC2: NTC2.2, R4.2, U1.30
SW1: C17.2, C19.2, C22.1, D6.1, D8.2, N1.7, N1.8, Q1.7, Q1.8
SW2: C18.1, C20.1, C21.1, D7.1, D9.2, N1.5, N1.6, Q1.5, Q1.6, W2.1, W2.e5, W2.e7, W2.e8, W2.e9
UPGATE1: R19.1, U1.54
UPGATE2: R21.2, U1.52
VBRIGE: C23.2, C24.2, D8.1, D9.1, D10.1, Q1.1, Q1.3, Q3.3, Q5.3, Q6.2, R18.2, R20.2, R34.2, R35.2
VBUS: C2.2, D2.2, T1.1, U1.19, U1.20, USB1.A4, USB1.A9, USB1.B4, USB1.B9
VCC: C13.2, D5.1, R14.2, R16.1, T5.1, U1.25
VDD: C14.2, U1.28
VSET: R7.2, U1.57
VSYS: C3.1, C4.2, C5.2, C6.2, C7.2, Q2.3, Q4.3, R35.1, U1.17, U1.18, U1.63, U1.64
V_DECODE: C27.1, U1.46
V_DET: C26.2, R30.1, R31.2, U1.47
